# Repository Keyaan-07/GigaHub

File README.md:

# GigaHub
GigaHub is a USB 3.0 Hub capable of speeds upto 5Gbps. It comes in a small form factor and can handle upto 4 devices simultaneously. The silkscreen on the bottom makes it obvious. You plug in the USB-C cable on one side, and you get 4x USB-C cables. 

I made this project just for fun and because i had some free time. I could've made USB 2.0 hub but this was a bit challenging thus i made this!!

[Onshape link](https://cad.onshape.com/documents/e81256595efe5e6b347fe7a8/w/0dcc8df7d91fb49fe0a745b9/e/4c090b9e2a0ff4ca85e35435)  
[Kicanvas link](https://kicanvas.org/?github=https://github.com/Keyaan-07/GigaHub/tree/main/hardware)  

# How to build

To Assemble this PCB, first you need to be familiar with soldering. You take your bare PCB, apply solder paste on it(soldering iron and solder is not recommended because it involves pins under the surface, such as the USB-C receptacles). Then, you take a hotplate or a hot air gun and melt the solder appropriately. There are many tutorials online teaching it in a great way, go search there!

The linked html file under /hardware/bom helps you with placement!

# BOM
|Designator                                                  |Function         |Value           |Footprint                                        |Quantity         |Price |Amount |Order|Note      |Link                                              |
|------------------------------------------------------------|-----------------|----------------|-------------------------------------------------|-----------------|------|-------|-----|----------|--------------------------------------------------|
|PCB                                                         |PCB              |4 layer board   |49.57mm x 34.54mm                                |5                |0.4   |2      |Yes  |          |https://jlcpcb.com/                               |
|C1, C10, C11, C2, C3, C4, C5, C6, C7, C8, C9                |Capacitor        |100n            |402                                              |11               |0.0077|0.0847 |No   |          |https://www.lcsc.com/product-detail/C426067.html  |
|C12, C13                                                    |Capacitor        |15p             |402                                              |50               |0.019 |0.95   |Yes  |50 is MOQ |https://www.lcsc.com/product-detail/C441742.html  |
|J1, J2, J3, J4, J5                                          |Receptacle       |USB_C_Receptacle|USB_C_Receptacle_Molex_105450-0101               |5                |0.29  |1.45   |Yes  |          |https://www.lcsc.com/product-detail/C48887178.html|
|R1                                                          |Resistor         |9.53k           |402                                              |100              |0.0008|0.08   |Yes  |100 is MOQ|https://www.lcsc.com/product-detail/C96273.html   |
|R2, R3, R4, R10, R11, R12, R13, R14, R15, R16, R17, R18, R19|Resistor         |5.1k            |402                                              |13               |0.0056|0.0728 |No   |          |https://www.lcsc.com/product-detail/C278598.html  |
|R5                                                          |Resistor         |10k             |402                                              |100              |0.0006|0.06   |Yes  |100 is MOQ|https://www.lcsc.com/product-detail/C3020235.html |
|R6                                                          |Resistor         |90.9k           |402                                              |100              |0.0006|0.06   |Yes  |100 is MOQ|https://www.lcsc.com/product-detail/C2998102.html |
|R7                                                          |Resistor         |1M              |402                                              |100              |0.0009|0.09   |Yes  |100 is MOQ|https://www.lcsc.com/product-detail/C138033.html  |
|R8, R9                                                      |Resistor         |30k             |402                                              |100              |0.0007|0.07   |Yes  |100 is MOQ|https://www.lcsc.com/product-detail/C2909347.html |
|U1                                                          |Hub Controller IC|TUSB8041        |QFN-64-1EP_9x9mm_P0.5mm_EP6x6mm_ThermalVias      |1                |4.83  |4.83   |Yes  |          |https://www.lcsc.com/product-detail/C544686.html  |
|U4, U5, U7, U7, U8                                          |Multiplexer IC   |HD3SS3220       |QFN-30-1EP                                       |5                |1.89  |9.44   |Yes  |          |https://www.lcsc.com/product-detail/C165155.html  |
|U2, U3                                                      |Power switch     |TPS2561         |VSON-10-1EP_3x3mm_P0.5mm_EP1.65x2.4mm_ThermalVias|2                |0.8   |1.6    |Yes  |          |https://www.lcsc.com/product-detail/C140303.html  |
|Y1                                                          |Crystal          |24 MHz          |Crystal_SMD_3225-4Pin_3.2x2.5mm                  |10               |0.036 |0.36   |Yes  |10 is MOQ |https://www.lcsc.com/product-detail/C41383243.html|
|                                                            |                 |                |                                                 |Shipping fee JLC |      |7.72   |     |          |                                                  |
|                                                            |                 |                |                                                 |Shipping fee LCSC|      |3.92   |     |          |                                                  |
|                                                            |                 |                |                                                 |Handling Fee LCSC|      |3      |     |          |                                                  |
|                                                            |                 |                |                                                 |Total            |      |35.7875|     |          |                                                  |

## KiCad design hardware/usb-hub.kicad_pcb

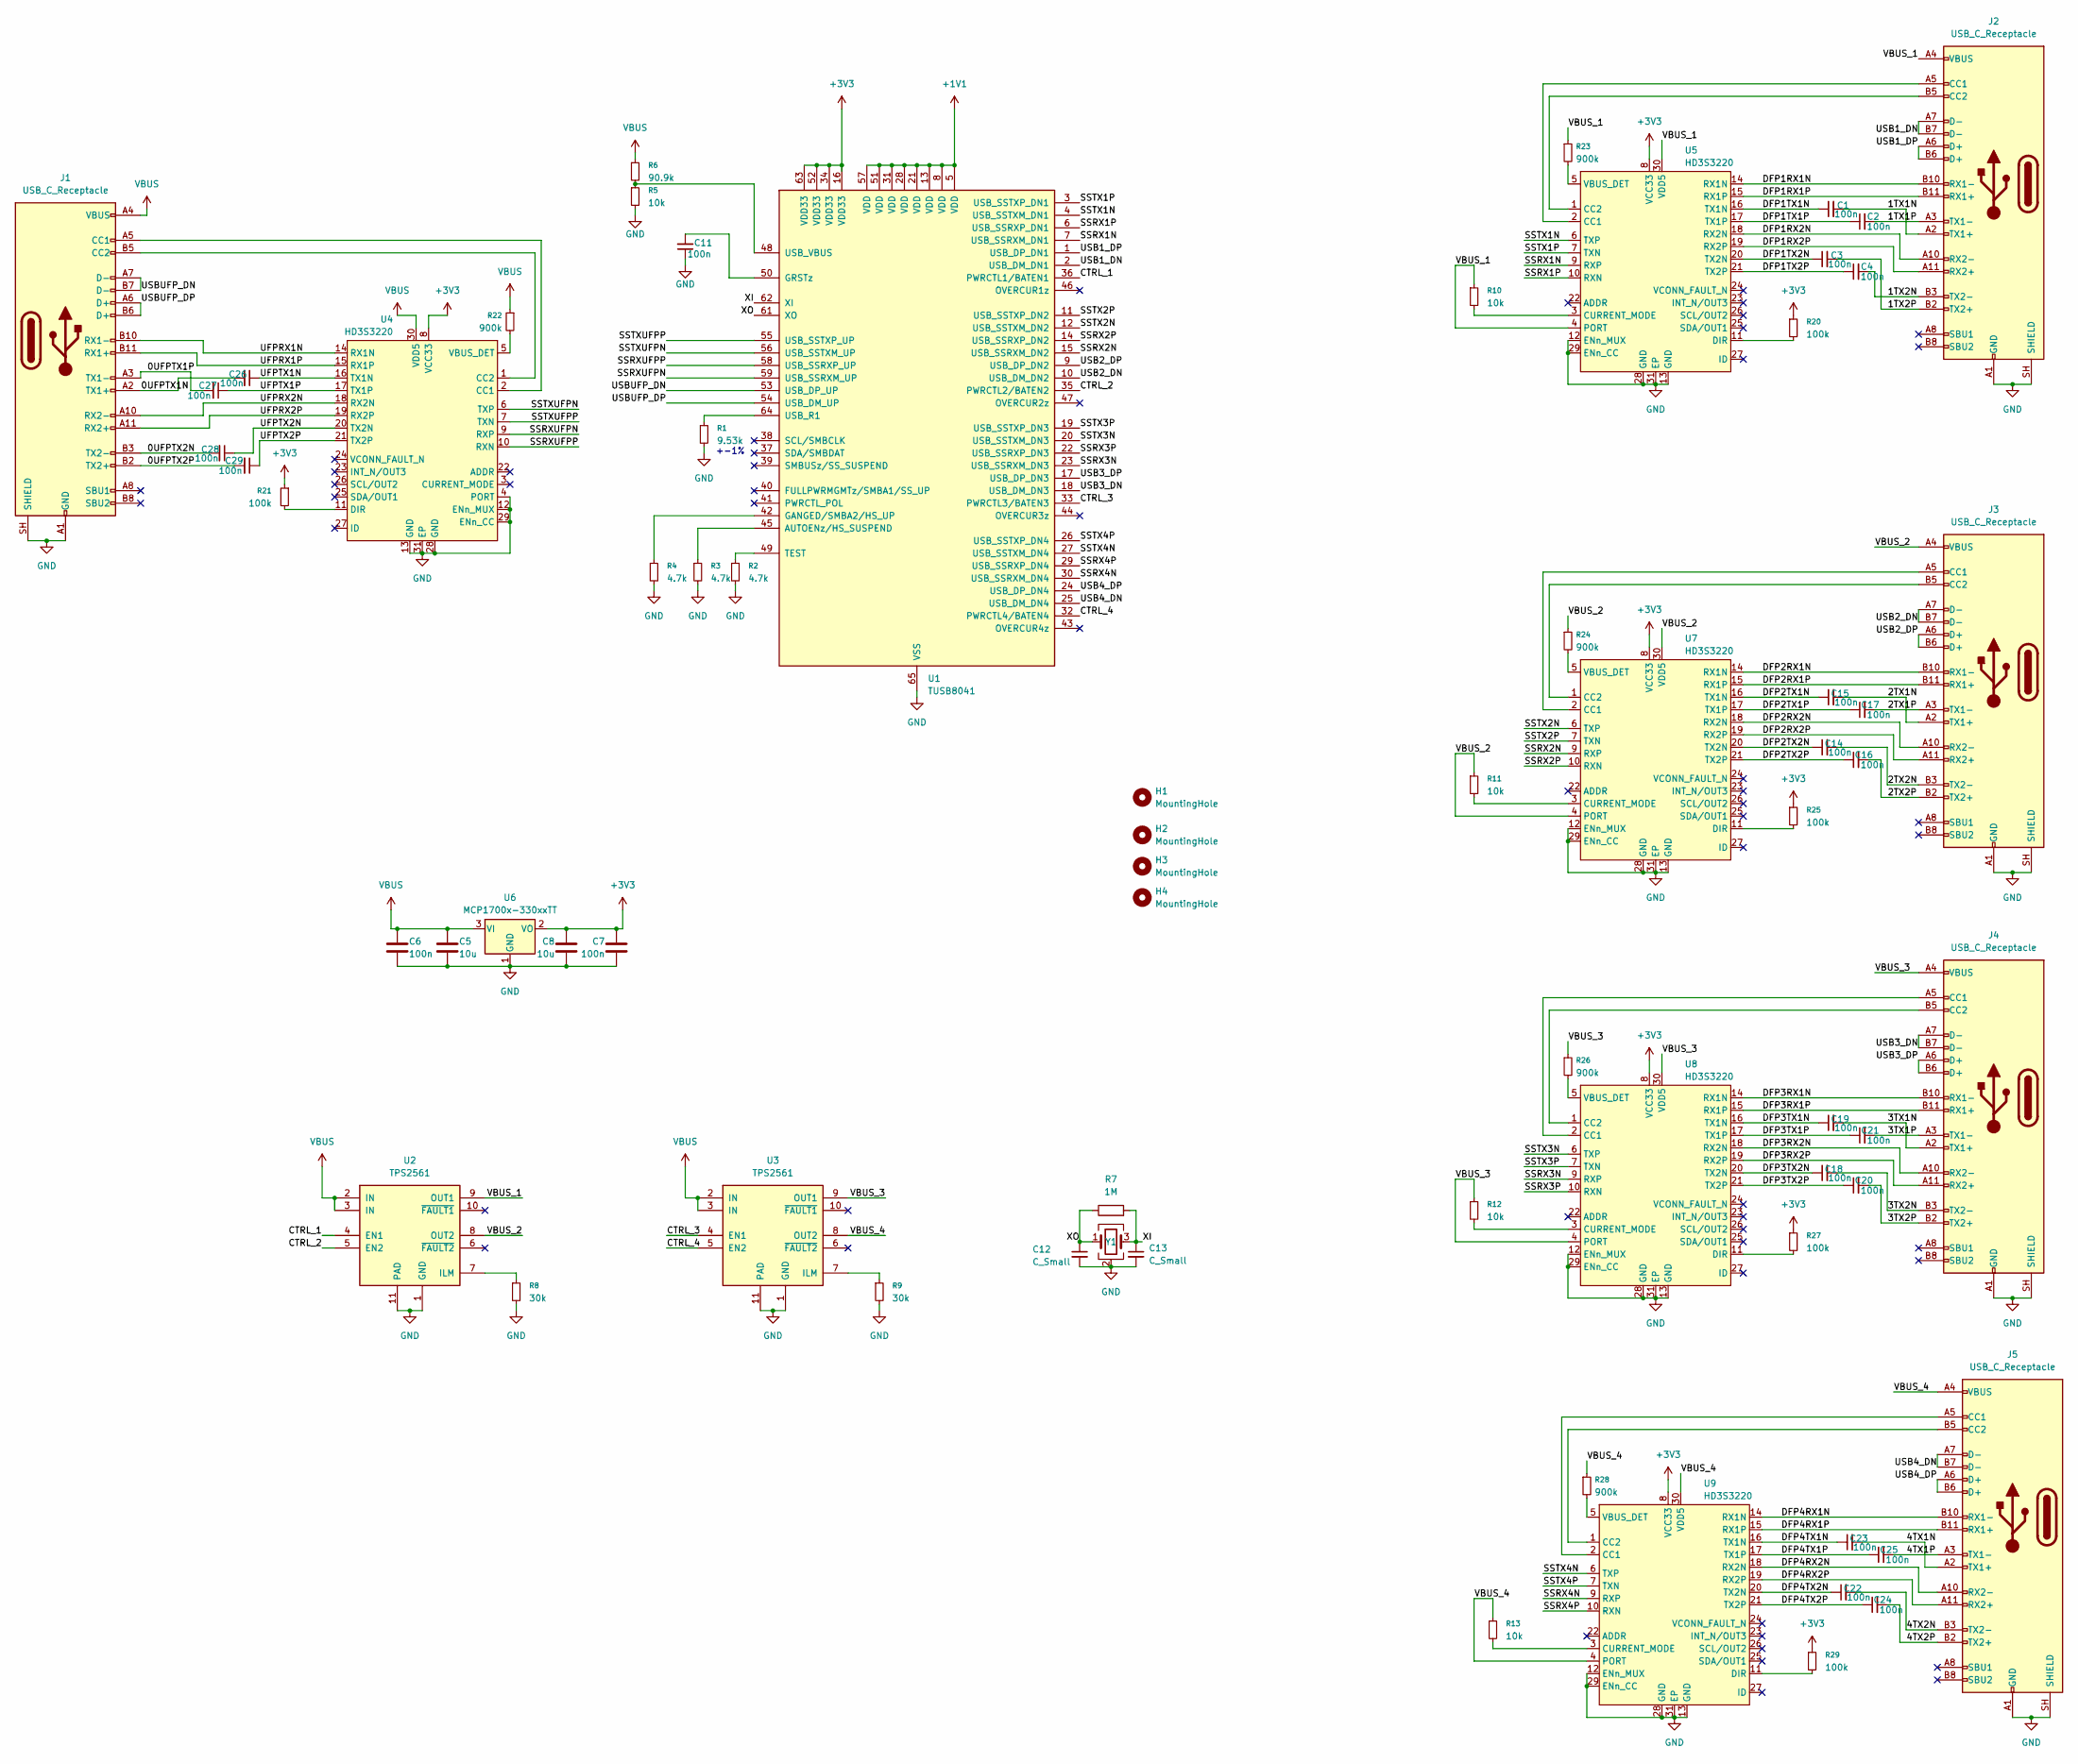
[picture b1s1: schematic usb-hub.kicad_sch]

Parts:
C1, C2, C3, C4, C6, C7, C11, C14, C15, C16, C17, C18, C19, C20, C21, C22, C23, C24, C25, C26, C27, C28, C29: 100n; C_0402_1005Metric
C5, C8: 10u; C_0603_1608Metric
C12, C13: C_Small; C_0402_1005Metric
H1, H2, H3, H4: MountingHole; MountingHole_2.2mm_M2
J1, J2, J3, J4, J5: USB_C_Receptacle; USB_C_Receptacle_Molex_105450-0101
R1: 9.53k; R_0402_1005Metric
R2, R3, R4: 4.7k; R_0402_1005Metric
R5, R10, R11, R12, R13: 10k; R_0402_1005Metric
R6: 90.9k; R_0402_1005Metric
R7: 1M; R_0402_1005Metric
R8, R9: 30k; R_0402_1005Metric
R20, R21, R25, R27, R29: 100k; R_0402_1005Metric
R22, R23, R24, R26, R28: 900k; R_0402_1005Metric
U1: TUSB8041; QFN-64-1EP_9x9mm_P0.5mm_EP6x6mm_ThermalVias
U2, U3: TPS2561; VSON-10-1EP_3x3mm_P0.5mm_EP1.65x2.4mm_ThermalVias
U4, U5, U7, U8, U9: HD3S3220; Texas_RNH0030A_WQFN-30-1EP_2.5x4.5mm_P0.4mm_EP1.2x3.2mm
U6: MCP1700x-330xxTT; SOT-23
Y1: Crystal_GND24; Crystal_SMD_3225-4Pin_3.2x2.5mm

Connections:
+1V1: U1.5 (VDD), U1.8 (VDD), U1.13 (VDD), U1.21 (VDD), U1.28 (VDD), U1.31 (VDD), U1.51 (VDD), U1.57 (VDD)
+3V3: C7.1, C8.1, R20.1, R21.1, R25.1, R27.1, R29.1, U1.16 (VDD33), U1.34 (VDD33), U1.52 (VDD33), U1.63 (VDD33), U4.8 (VCC33), U5.8 (VCC33), U6.2 (VO), U7.8 (VCC33), U8.8 (VCC33), U9.8 (VCC33)
/0UFPTX1N: C26.2, J1.A2 (TX1+)
/0UFPTX1P: C27.2, J1.A3 (TX1-)
/0UFPTX2N: C28.2, J1.B3 (TX2-)
/0UFPTX2P: C29.2, J1.B2 (TX2+)
/1TX1N: C1.2, J2.A2 (TX1+)
/1TX1P: C2.2, J2.A3 (TX1-)
/1TX2N: C4.2, J2.B3 (TX2-)
/1TX2P: C3.2, J2.B2 (TX2+)
/2TX1N: C15.2, J3.A2 (TX1+)
/2TX1P: C17.2, J3.A3 (TX1-)
/2TX2N: C14.2, J3.B3 (TX2-)
/2TX2P: C16.2, J3.B2 (TX2+)
/3TX1N: C19.2, J4.A2 (TX1+)
/3TX1P: C21.2, J4.A3 (TX1-)
/3TX2N: C18.2, J4.B3 (TX2-)
/3TX2P: C20.2, J4.B2 (TX2+)
/4TX1N: C23.2, J5.A2 (TX1+)
/4TX1P: C25.2, J5.A3 (TX1-)
/4TX2N: C22.2, J5.B3 (TX2-)
/4TX2P: C24.2, J5.B2 (TX2+)
/CTRL_1: U1.36 (PWRCTL1/BATEN1), U2.4 (EN1)
/CTRL_2: U1.35 (PWRCTL2/BATEN2), U2.5 (EN2)
/CTRL_3: U1.33 (PWRCTL3/BATEN3), U3.4 (EN1)
/CTRL_4: U1.32 (PWRCTL4/BATEN4), U3.5 (EN2)
/DFP1RX1N: J2.B10 (RX1-), U5.14 (RX1N)
/DFP1RX1P: J2.B11 (RX1+), U5.15 (RX1P)
/DFP1RX2N: J2.A10 (RX2-), U5.18 (RX2N)
/DFP1RX2P: J2.A11 (RX2+), U5.19 (RX2P)
/DFP1TX1N: C1.1, U5.16 (TX1N)
/DFP1TX1P: C2.1, U5.17 (TX1P)
/DFP1TX2N: C3.1, U5.20 (TX2N)
/DFP1TX2P: C4.1, U5.21 (TX2P)
/DFP2RX1N: J3.B10 (RX1-), U7.14 (RX1N)
/DFP2RX1P: J3.B11 (RX1+), U7.15 (RX1P)
/DFP2RX2N: J3.A10 (RX2-), U7.18 (RX2N)
/DFP2RX2P: J3.A11 (RX2+), U7.19 (RX2P)
/DFP2TX1N: C15.1, U7.16 (TX1N)
/DFP2TX1P: C17.1, U7.17 (TX1P)
/DFP2TX2N: C14.1, U7.20 (TX2N)
/DFP2TX2P: C16.1, U7.21 (TX2P)
/DFP3RX1N: J4.B10 (RX1-), U8.14 (RX1N)
/DFP3RX1P: J4.B11 (RX1+), U8.15 (RX1P)
/DFP3RX2N: J4.A10 (RX2-), U8.18 (RX2N)
/DFP3RX2P: J4.A11 (RX2+), U8.19 (RX2P)
/DFP3TX1N: C19.1, U8.16 (TX1N)
/DFP3TX1P: C21.1, U8.17 (TX1P)
/DFP3TX2N: C18.1, U8.20 (TX2N)
/DFP3TX2P: C20.1, U8.21 (TX2P)
/DFP4RX1N: J5.B10 (RX1-), U9.14 (RX1N)
/DFP4RX1P: J5.B11 (RX1+), U9.15 (RX1P)
/DFP4RX2N: J5.A10 (RX2-), U9.18 (RX2N)
/DFP4RX2P: J5.A11 (RX2+), U9.19 (RX2P)
/DFP4TX1N: C23.1, U9.16 (TX1N)
/DFP4TX1P: C25.1, U9.17 (TX1P)
/DFP4TX2N: C22.1, U9.20 (TX2N)
/DFP4TX2P: C24.1, U9.21 (TX2P)
/SSRX1N: U1.7 (USB_SSRXM_DN1), U5.9 (RXP)
/SSRX1P: U1.6 (USB_SSRXP_DN1), U5.10 (RXN)
/SSRX2N: U1.15 (USB_SSRXM_DN2), U7.9 (RXP)
/SSRX2P: U1.14 (USB_SSRXP_DN2), U7.10 (RXN)
/SSRX3N: U1.23 (USB_SSRXM_DN3), U8.9 (RXP)
/SSRX3P: U1.22 (USB_SSRXP_DN3), U8.10 (RXN)
/SSRX4N: U1.30 (USB_SSRXM_DN4), U9.9 (RXP)
/SSRX4P: U1.29 (USB_SSRXP_DN4), U9.10 (RXN)
/SSRXUFPN: U1.59 (USB_SSRXM_UP), U4.9 (RXP)
/SSRXUFPP: U1.58 (USB_SSRXP_UP), U4.10 (RXN)
/SSTX1N: U1.4 (USB_SSTXM_DN1), U5.6 (TXP)
/SSTX1P: U1.3 (USB_SSTXP_DN1), U5.7 (TXN)
/SSTX2N: U1.12 (USB_SSTXM_DN2), U7.6 (TXP)
/SSTX2P: U1.11 (USB_SSTXP_DN2), U7.7 (TXN)
/SSTX3N: U1.20 (USB_SSTXM_DN3), U8.6 (TXP)
/SSTX3P: U1.19 (USB_SSTXP_DN3), U8.7 (TXN)
/SSTX4N: U1.27 (USB_SSTXM_DN4), U9.6 (TXP)
/SSTX4P: U1.26 (USB_SSTXP_DN4), U9.7 (TXN)
/SSTXUFPN: U1.56 (USB_SSTXM_UP), U4.6 (TXP)
/SSTXUFPP: U1.55 (USB_SSTXP_UP), U4.7 (TXN)
/UFPRX1N: J1.B10 (RX1-), U4.14 (RX1N)
/UFPRX1P: J1.B11 (RX1+), U4.15 (RX1P)
/UFPRX2N: J1.A10 (RX2-), U4.18 (RX2N)
/UFPRX2P: J1.A11 (RX2+), U4.19 (RX2P)
/UFPTX1N: C26.1, U4.16 (TX1N)
/UFPTX1P: C27.1, U4.17 (TX1P)
/UFPTX2N: C28.1, U4.20 (TX2N)
/UFPTX2P: C29.1, U4.21 (TX2P)
/USB1_DN: J2.A7 (D-), J2.B7 (D-), U1.2 (USB_DM_DN1)
/USB1_DP: J2.A6 (D+), J2.B6 (D+), U1.1 (USB_DP_DN1)
/USB2_DN: J3.A7 (D-), J3.B7 (D-), U1.10 (USB_DM_DN2)
/USB2_DP: J3.A6 (D+), J3.B6 (D+), U1.9 (USB_DP_DN2)
/USB3_DN: J4.A7 (D-), J4.B7 (D-), U1.18 (USB_DM_DN3)
/USB3_DP: J4.A6 (D+), J4.B6 (D+), U1.17 (USB_DP_DN3)
/USB4_DN: J5.A7 (D-), J5.B7 (D-), U1.25 (USB_DM_DN4)
/USB4_DP: J5.A6 (D+), J5.B6 (D+), U1.24 (USB_DP_DN4)
/USBUFP_DN: J1.A7 (D-), J1.B7 (D-), U1.53 (USB_DP_UP)
/USBUFP_DP: J1.A6 (D+), J1.B6 (D+), U1.54 (USB_DM_UP)
/VBUS_1: J2.A4 (VBUS), J2.A9 (VBUS), J2.B4 (VBUS), J2.B9 (VBUS), R10.1, R23.1, U2.9 (OUT1), U5.4 (PORT), U5.30 (VDD5)
/VBUS_2: J3.A4 (VBUS), J3.A9 (VBUS), J3.B4 (VBUS), J3.B9 (VBUS), R11.1, R24.1, U2.8 (OUT2), U7.4 (PORT), U7.30 (VDD5)
/VBUS_3: J4.A4 (VBUS), J4.A9 (VBUS), J4.B4 (VBUS), J4.B9 (VBUS), R12.1, R26.1, U3.9 (OUT1), U8.4 (PORT), U8.30 (VDD5)
/VBUS_4: J5.A4 (VBUS), J5.A9 (VBUS), J5.B4 (VBUS), J5.B9 (VBUS), R13.1, R28.1, U3.8 (OUT2), U9.4 (PORT), U9.30 (VDD5)
/XI: C13.1, R7.2, U1.62 (XI), Y1.3
/XO: C12.1, R7.1, U1.61 (XO), Y1.1
GND: C5.2, C6.2, C7.2, C8.2, C11.1, C12.2, C13.2, J1.A1 (GND), J1.A12 (GND), J1.B1 (GND), J1.B12 (GND), J1.SH (SHIELD), J2.A1 (GND), J2.A12 (GND), J2.B1 (GND), J2.B12 (GND), J2.SH (SHIELD), J3.A1 (GND), J3.A12 (GND), J3.B1 (GND), J3.B12 (GND), J3.SH (SHIELD), J4.A1 (GND), J4.A12 (GND), J4.B1 (GND), J4.B12 (GND), J4.SH (SHIELD), J5.A1 (GND), J5.A12 (GND), J5.B1 (GND), J5.B12 (GND), J5.SH (SHIELD), R1.2, R2.2, R3.2, R4.2, R5.2, R8.2, R9.2, U1.65 (VSS), U2.1 (GND), U2.11 (PAD), U3.1 (GND), U3.11 (PAD), U4.4 (PORT), U4.12 (ENn_MUX), U4.13 (GND), U4.28 (GND), U4.29 (ENn_CC), U4.31 (EP), U5.12 (ENn_MUX), U5.13 (GND), U5.28 (GND), U5.29 (ENn_CC), U5.31 (EP), U6.1 (GND), U7.12 (ENn_MUX), U7.13 (GND), U7.28 (GND), U7.29 (ENn_CC), U7.31 (EP), U8.12 (ENn_MUX), U8.13 (GND), U8.28 (GND), U8.29 (ENn_CC), U8.31 (EP), U9.12 (ENn_MUX), U9.13 (GND), U9.28 (GND), U9.29 (ENn_CC), U9.31 (EP), Y1.2 (G), Y1.4 (G)
unnamed: J1.A5 (CC1), U4.2 (CC1)
unnamed: J1.B5 (CC2), U4.1 (CC2)
unnamed: J2.A5 (CC1), U5.2 (CC1)
unnamed: J2.B5 (CC2), U5.1 (CC2)
unnamed: J3.A5 (CC1), U7.2 (CC1)
unnamed: J3.B5 (CC2), U7.1 (CC2)
unnamed: J4.A5 (CC1), U8.2 (CC1)
unnamed: J4.B5 (CC2), U8.1 (CC2)
unnamed: J5.A5 (CC1), U9.2 (CC1)
unnamed: J5.B5 (CC2), U9.1 (CC2)
unnamed: R3.1, U1.45 (AUTOENz/HS_SUSPEND)
unnamed: R4.1, U1.42 (GANGED/SMBA2/HS_UP)
unnamed: C11.2, U1.50 (GRSTz)
unnamed: R2.1, U1.49 (TEST)
unnamed: R1.1, U1.64 (USB_R1)
unnamed: R5.1, R6.2, U1.48 (USB_VBUS)
unnamed: R8.1, U2.7 (ILM)
unnamed: R9.1, U3.7 (ILM)
unnamed: R21.2, U4.11 (DIR)
unnamed: R22.2, U4.5 (VBUS_DET)
unnamed: R10.2, U5.3 (CURRENT_MODE)
unnamed: R20.2, U5.11 (DIR)
unnamed: R23.2, U5.5 (VBUS_DET)
unnamed: R11.2, U7.3 (CURRENT_MODE)
unnamed: R25.2, U7.11 (DIR)
unnamed: R24.2, U7.5 (VBUS_DET)
unnamed: R12.2, U8.3 (CURRENT_MODE)
unnamed: R27.2, U8.11 (DIR)
unnamed: R26.2, U8.5 (VBUS_DET)
unnamed: R13.2, U9.3 (CURRENT_MODE)
unnamed: R29.2, U9.11 (DIR)
unnamed: R28.2, U9.5 (VBUS_DET)
VBUS: C5.1, C6.1, J1.A4 (VBUS), J1.A9 (VBUS), J1.B4 (VBUS), J1.B9 (VBUS), R6.1, R22.1, U2.2 (IN), U2.3 (IN), U3.2 (IN), U3.3 (IN), U4.30 (VDD5), U6.3 (VI)

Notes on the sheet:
+-1%

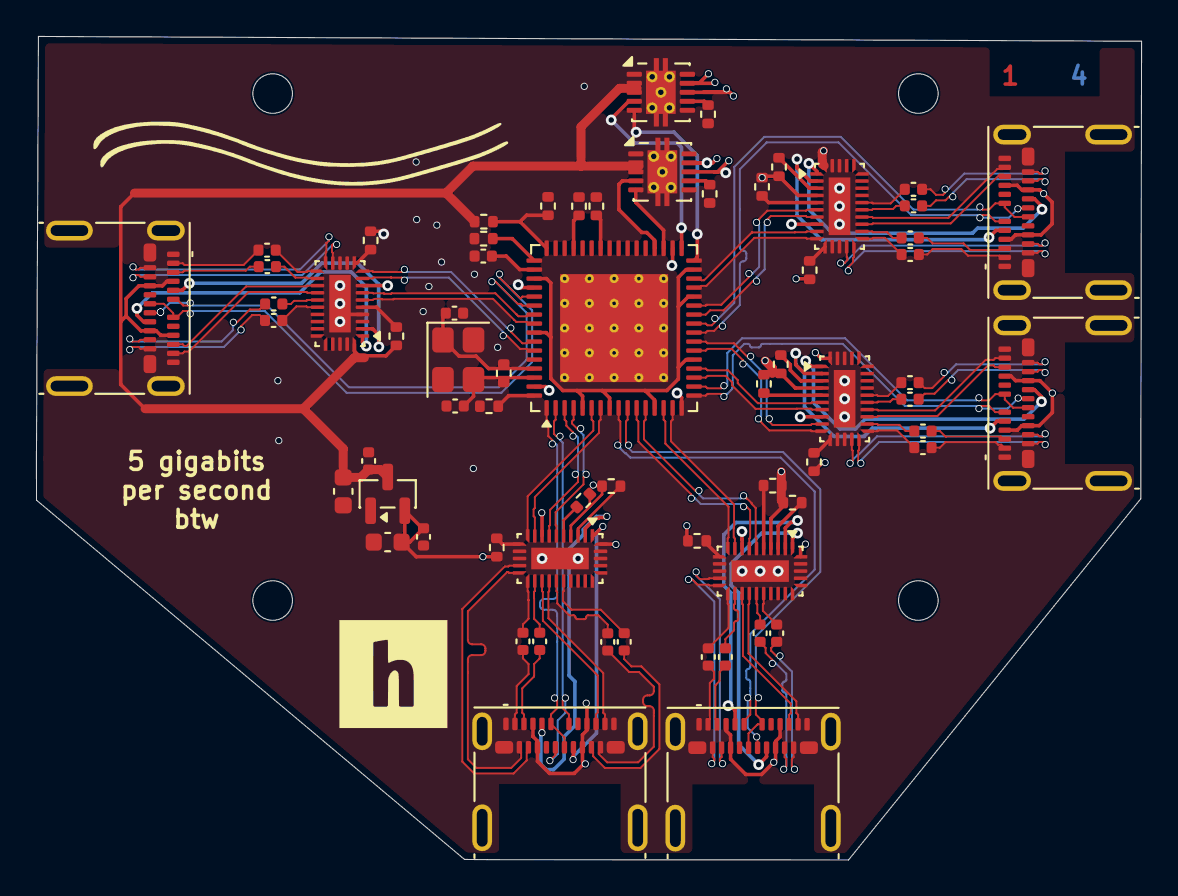
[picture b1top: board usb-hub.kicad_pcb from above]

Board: 4 copper layers, 61.4 x 45.8 mm, 69 parts (0 on the bottom side), 136 nets.

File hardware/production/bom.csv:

Designator,Footprint,Quantity,Value,LCSC Part #
"C1, C11, C14, C15, C16, C17, C18, C19, C2, C20, C21, C22, C23, C24, C25, C26, C27, C28, C29, C3, C4, C6, C7",0402,23,100n,
"C12, C13",0402,2,C_Small,
"C5, C8",0603,2,10u,
"J1, J2, J3, J4, J5",USB_C_Receptacle_Molex_105450-0101,5,USB_C_Receptacle,
R1,0402,1,9.53k,
"R10, R11, R12, R13, R5",0402,5,10k,
"R2, R3, R4",0402,3,4.7k,
"R20, R21, R25, R27, R29",0402,5,100k,
"R22, R23, R24, R26, R28",0402,5,900k,
R6,0402,1,90.9k,
R7,0402,1,1M,
"R8, R9",0402,2,30k,
U1,QFN-64-1EP_9x9mm_P0.5mm_EP6x6mm_ThermalVias,1,TUSB8041,
"U2, U3",VSON-10-1EP_3x3mm_P0.5mm_EP1.65x2.4mm_ThermalVias,2,TPS2561,
"U4, U5, U7, U8, U9",Texas_RNH0030A_WQFN-30-1EP_2.5x4.5mm_P0.4mm_EP1.2x3.2mm,5,HD3S3220,
U6,SOT-23,1,MCP1700x-330xxTT,
Y1,Crystal_SMD_3225-4Pin_3.2x2.5mm,1,Crystal_GND24,

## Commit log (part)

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2026-05-18 Hello World
2026-05-20 images added
2026-05-20 Bill of Materials
2026-05-20 final files
2026-05-20 Readme updates
2026-05-20 Create LICENSE
2026-05-20 magazine page
2026-05-20 Soldering info
2026-05-20 Why i made ts
2026-06-26 added new images
2026-06-26 added more images
2026-06-26 PCB Changed
2026-06-26 updated BOM
2026-06-26 update BOM
2026-06-26 add CAD files for assembly
2026-06-26 added schematic image
2026-06-26 add top case image
2026-06-26 added latest production files
2026-06-27 latest production files
2026-06-27 removed backups
